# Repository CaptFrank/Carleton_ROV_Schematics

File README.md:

Carleton_ROV_Schematics
=======================

ROV schematics

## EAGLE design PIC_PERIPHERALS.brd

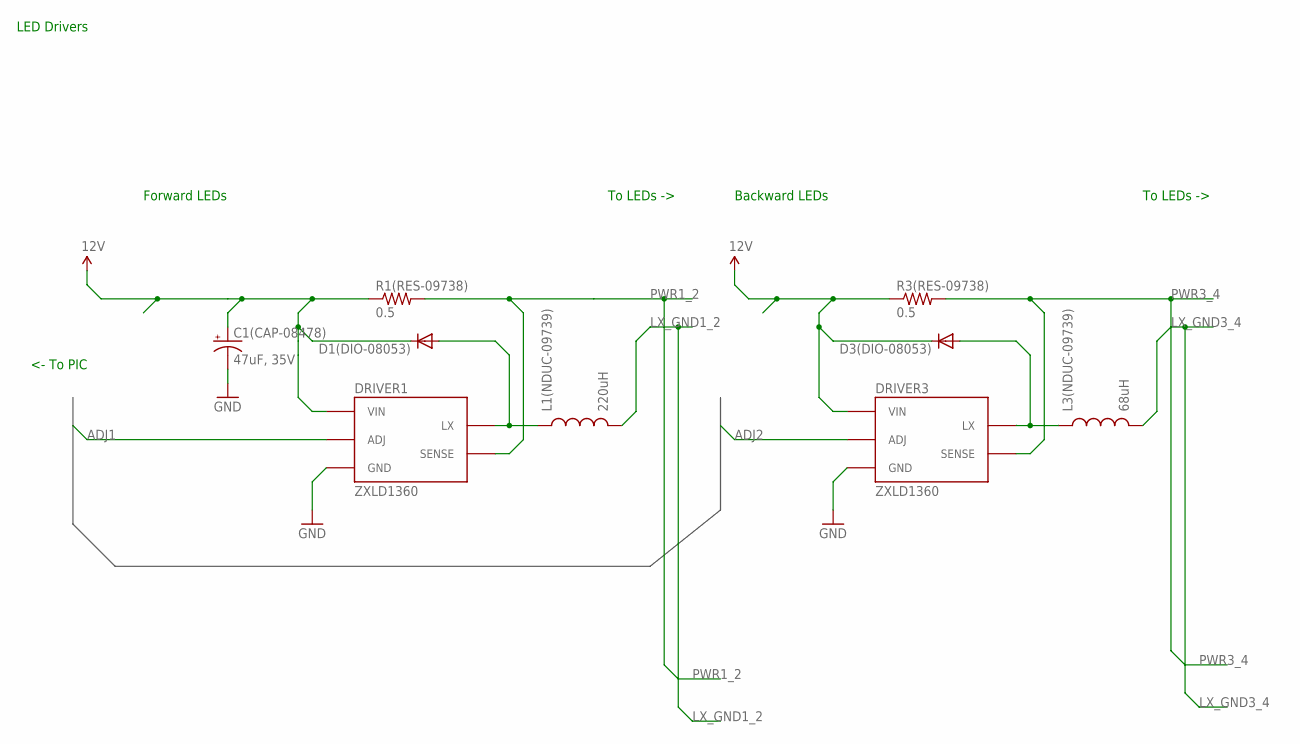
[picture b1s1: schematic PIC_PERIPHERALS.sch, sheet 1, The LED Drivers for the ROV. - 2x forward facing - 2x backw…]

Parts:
C1(CAP-08478): 47uF, 35V; EIA3216
D1(DIO-08053), D3(DIO-08053): DIODESMA; SMA-DIODE
DRIVER1, DRIVER3: ZXLD1360; SOT23-5
L1(NDUC-09739): 220uH; CDRH3D28
L3(NDUC-09739): 68uH; CDRH3D28
R1(RES-09738), R3(RES-09738): 0.5; 0805

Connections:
5V: D3(DIO-08053).C, DRIVER3.5 (VIN), R3(RES-09738).1; also elsewhere on the board
12V: C1(CAP-08478).A (+), D1(DIO-08053).C, DRIVER1.5 (VIN), R1(RES-09738).1
ADJ1: DRIVER1.3 (ADJ); also elsewhere on the board
ADJ2: DRIVER3.3 (ADJ); also elsewhere on the board
GND: C1(CAP-08478).C (-), DRIVER1.2 (GND), DRIVER3.2 (GND); also elsewhere on the board
LX_GND1_2: L1(NDUC-09739).2
LX_GND3_4: L3(NDUC-09739).2
unnamed: D1(DIO-08053).A, DRIVER1.1 (LX), L1(NDUC-09739).1
unnamed: D3(DIO-08053).A, DRIVER3.1 (LX), L3(NDUC-09739).1
PWR1_2: DRIVER1.4 (SENSE), R1(RES-09738).2
PWR3_4: DRIVER3.4 (SENSE), R3(RES-09738).2

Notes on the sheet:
LED Drivers
Forward LEDs
Backward LEDs
<- To PIC
To LEDs ->

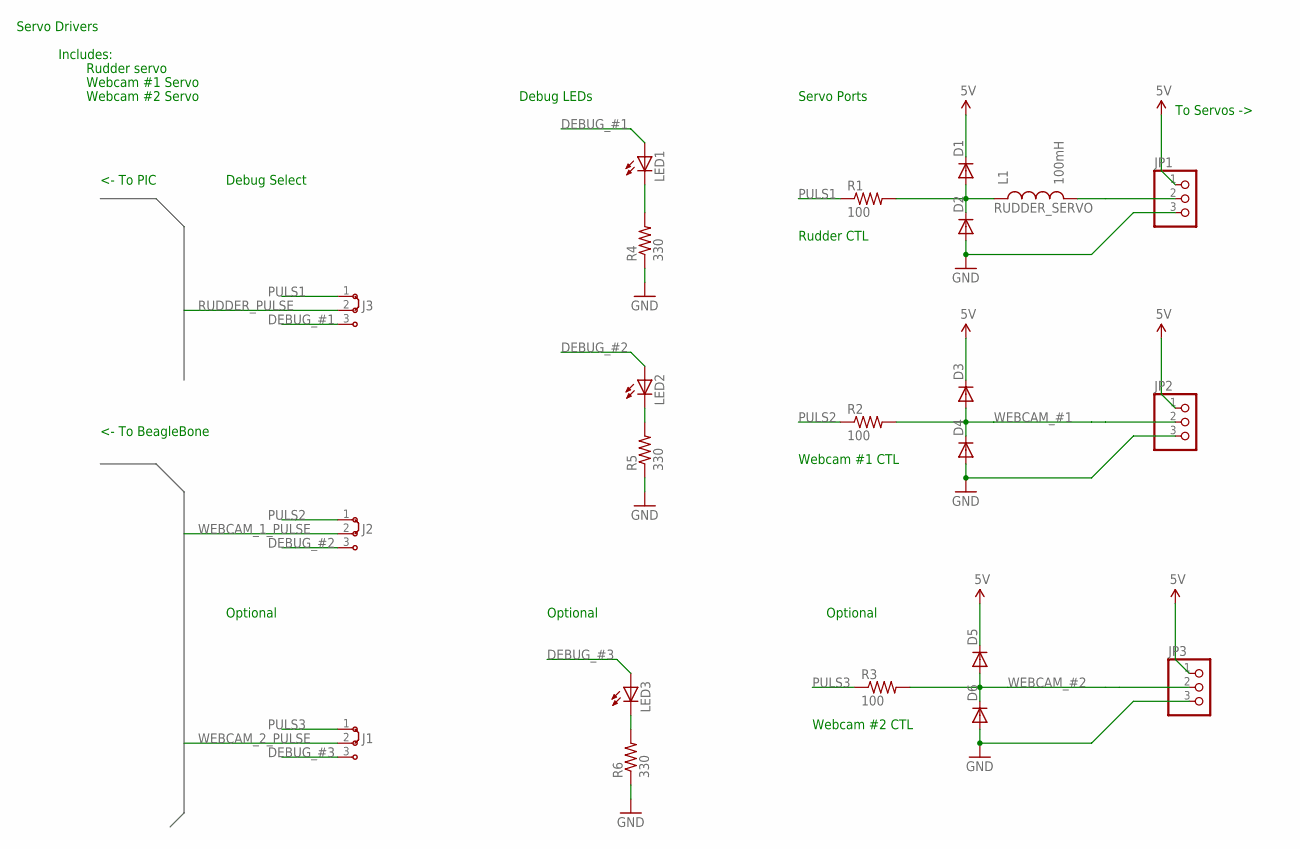
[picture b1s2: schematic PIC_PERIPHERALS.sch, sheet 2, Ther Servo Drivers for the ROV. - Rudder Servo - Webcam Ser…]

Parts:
D1, D2, D3, D4, D5, D6: DIODESMA-ALT; SMA-DIODE_ALT
J1, J2, J3: J2X2MM; 04C
JP1, JP2, JP3: PINHD-1X3CB; 1X03-CLEANBIG
L1: 100mH; 0805
LED1, LED2, LED3: LED; SMARTLED-TTW
R1, R2, R3: 100; 0402-RES
R4, R5, R6: 330; 0402-RES

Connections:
5V: D1.C, D3.C, D5.C, JP1.1, JP2.1, JP3.1; also elsewhere on the board
DEBUG_#1: J3.3, LED1.A@1 (A)
DEBUG_#2: J2.3, LED2.A@1 (A)
DEBUG_#3: J1.3, LED3.A@1 (A)
GND: D2.A, D4.A, D6.A, JP1.3, JP2.3, JP3.3, R4.1, R5.1, R6.1; also elsewhere on the board
unnamed: LED1.C@1 (C), R4.2
unnamed: LED2.C@1 (C), R5.2
unnamed: LED3.C@1 (C), R6.2
PULS1: J3.1, R1.1
PULS2: J2.1, R2.1
PULS3: J1.1, R3.1
RUDDER_PULSE: J3.2; also elsewhere on the board
RUDDER_SERVO: JP1.2, L1.2
RUDDER_SERVO1: D1.A, D2.C, L1.1, R1.2
WEBCAM_1_PULSE: J2.2; also elsewhere on the board
WEBCAM_2_PULSE: J1.2; also elsewhere on the board
WEBCAM_#1: D3.A, D4.C, JP2.2, R2.2
WEBCAM_#2: D5.A, D6.C, JP3.2, R3.2

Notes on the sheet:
Servo Drivers
Includes:
Rudder servo
Webcam #1 Servo
Webcam #2 Servo
To Servos ->
<- To PIC
Debug LEDs
Servo Ports
Debug Select
Rudder CTL
Webcam #1 CTL
Webcam #2 CTL
Optional
<- To BeagleBone

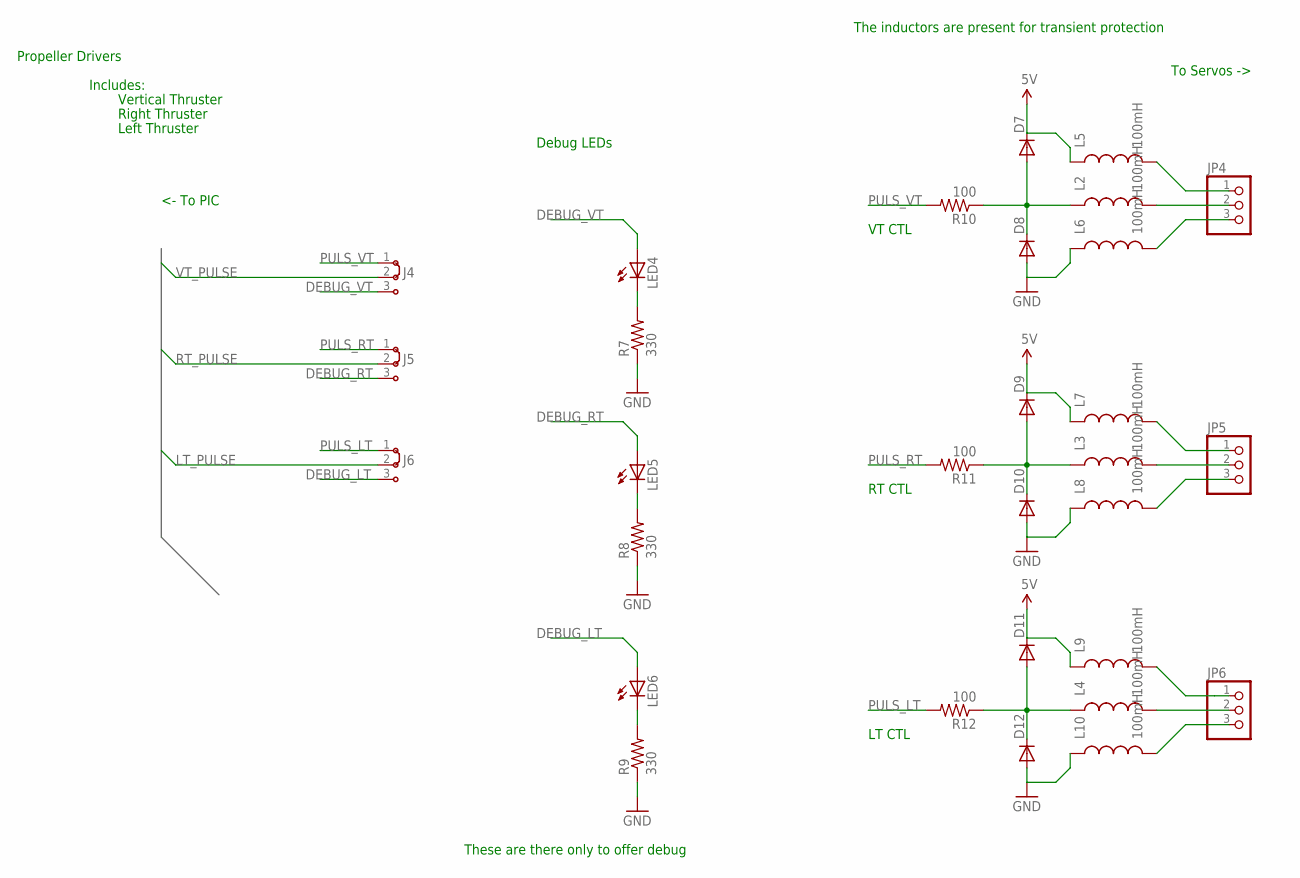
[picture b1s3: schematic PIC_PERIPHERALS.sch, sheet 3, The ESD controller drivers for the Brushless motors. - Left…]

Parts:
D7, D8, D9, D10, D11, D12: DIODESMA; SMA-DIODE
J4, J5, J6: J2X2MM; 04C
JP4, JP5, JP6: PINHD-1X3CB; 1X03-CLEANBIG
L2, L3, L4, L5, L6, L7, L8, L9, L10: 100mH; 0603
LED4, LED5, LED6: LED; SMARTLED-TTW
R7, R8, R9: 330; 0402-RES
R10, R11, R12: 100; 0402-RES

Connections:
5V: D7.C, D9.C, D11.C, L5.1, L7.1, L9.1; also elsewhere on the board
DEBUG_LT: J6.3, LED6.A@1 (A)
DEBUG_RT: J5.3, LED5.A@1 (A)
DEBUG_VT: J4.3, LED4.A@1 (A)
GND: D8.A, D10.A, D12.A, L6.1, L8.1, L10.1, R7.1, R8.1, R9.1; also elsewhere on the board
LT_PULSE: J6.2; also elsewhere on the board
unnamed: LED4.C@1 (C), R7.2
unnamed: LED5.C@1 (C), R8.2
unnamed: LED6.C@1 (C), R9.2
unnamed: D11.A, D12.C, L4.1, R12.1
unnamed: D9.A, D10.C, L3.1, R11.1
unnamed: D7.A, D8.C, L2.1, R10.1
unnamed: JP4.1, L5.2
unnamed: JP4.2, L2.2
unnamed: JP4.3, L6.2
unnamed: JP5.1, L7.2
unnamed: JP5.2, L3.2
unnamed: JP5.3, L8.2
unnamed: JP6.1, L9.2
unnamed: JP6.2, L4.2
unnamed: JP6.3, L10.2
PULS_LT: J6.1, R12.2
PULS_RT: J5.1, R11.2
PULS_VT: J4.1, R10.2
RT_PULSE: J5.2; also elsewhere on the board
VT_PULSE: J4.2; also elsewhere on the board

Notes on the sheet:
Propeller Drivers
Includes:
Vertical Thruster
Right Thruster
Left Thruster
To Servos ->
Debug LEDs
<- To PIC
VT CTL
LT CTL
RT CTL
The inductors are present for transient protection
These are there only to offer debug

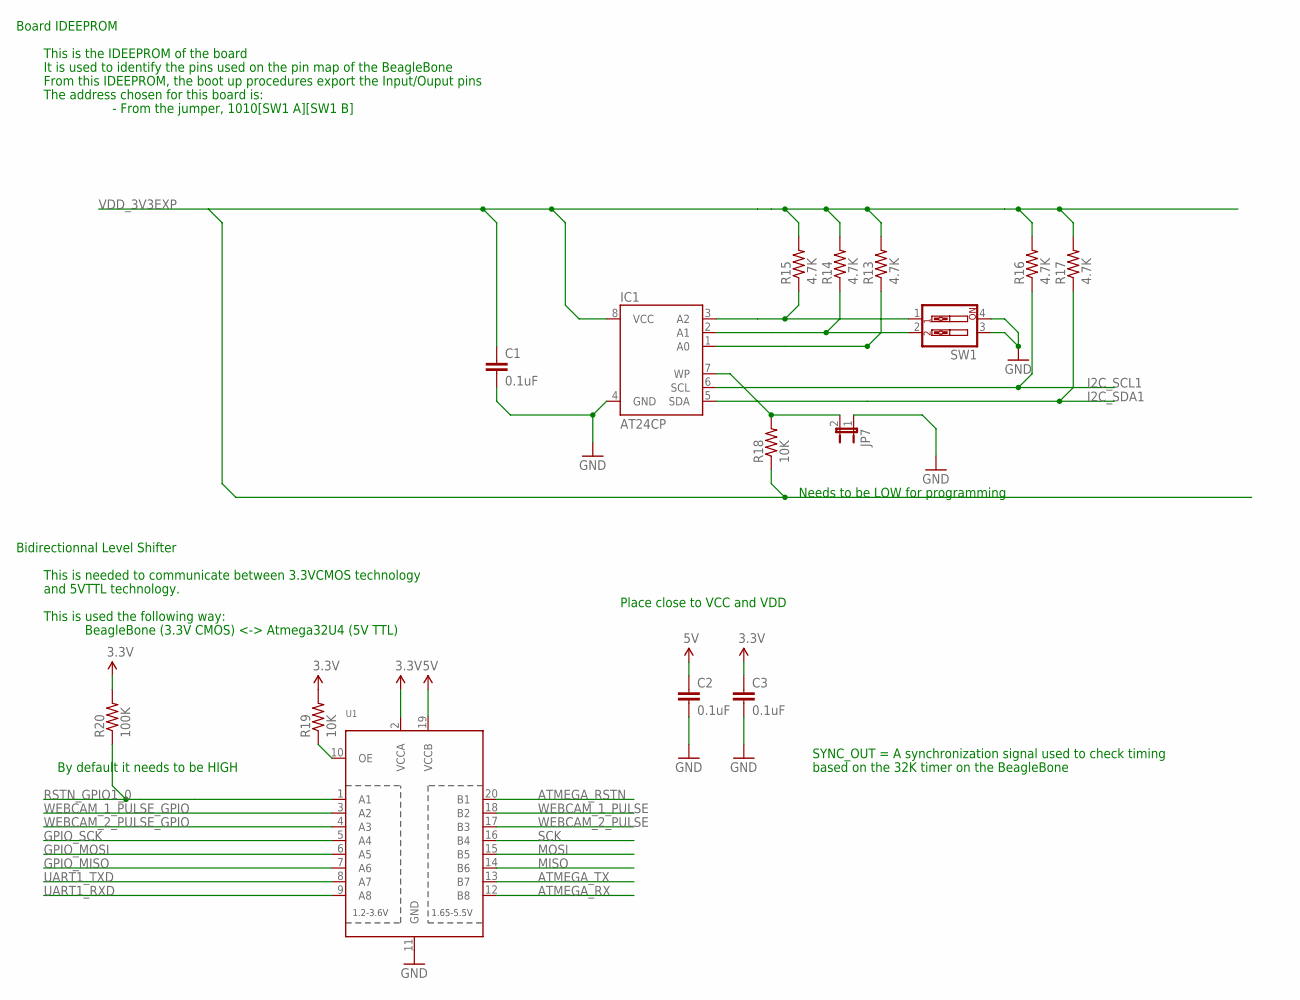
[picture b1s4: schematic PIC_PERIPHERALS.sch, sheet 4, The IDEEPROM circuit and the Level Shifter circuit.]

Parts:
C1, C2, C3: 0.1uF; 0402-CAP
IC1: AT24CP; DIL08
JP7: JUMPER-2PTH; 1X02
R13, R14, R15, R16, R17: 4.7K; 0402-RES
R18, R19: 10K; 0402-RES
R20: 100K; 0402-RES
SW1: SW_DIP-2; DIPSWITCH-02
U1: TXB0108PWR; TSSOP20

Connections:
3.3V: C3.1, R19.2, R20.2, U1.2 (VCCA); also elsewhere on the board
5V: C2.1, U1.19 (VCCB); also elsewhere on the board
ATMEGA_RSTN: U1.20 (B1); also elsewhere on the board
ATMEGA_RX: U1.12 (B8); also elsewhere on the board
ATMEGA_TX: U1.13 (B7); also elsewhere on the board
GND: C1.2, C2.2, C3.2, IC1.4 (GND), JP7.1, SW1.3, SW1.4, U1.11 (GND); also elsewhere on the board
GPIO_MISO: U1.7 (A6); also elsewhere on the board
GPIO_MOSI: U1.6 (A5); also elsewhere on the board
GPIO_SCK: U1.5 (A4); also elsewhere on the board
I2C_SCL1: IC1.6 (SCL), R16.1; also elsewhere on the board
I2C_SDA1: IC1.5 (SDA), R17.1; also elsewhere on the board
MISO: U1.14 (B6); also elsewhere on the board
MOSI: U1.15 (B5); also elsewhere on the board
unnamed: IC1.3 (A2), R15.1, SW1.1
unnamed: IC1.2 (A1), R14.1, SW1.2
unnamed: IC1.1 (A0), R13.1
unnamed: IC1.7 (WP), JP7.2, R18.2
unnamed: R19.1, U1.10 (OE)
RSTN_GPIO1_0: R20.1, U1.1 (A1); also elsewhere on the board
SCK: U1.16 (B4); also elsewhere on the board
UART1_RXD: U1.9 (A8); also elsewhere on the board
UART1_TXD: U1.8 (A7); also elsewhere on the board
VDD_3V3EXP: C1.1, IC1.8 (VCC), R13.2, R14.2, R15.2, R16.2, R17.2, R18.1
WEBCAM_1_PULSE: U1.18 (B2); also elsewhere on the board
WEBCAM_1_PULSE_GPIO: U1.3 (A2); also elsewhere on the board
WEBCAM_2_PULSE: U1.17 (B3); also elsewhere on the board
WEBCAM_2_PULSE_GPIO: U1.4 (A3); also elsewhere on the board

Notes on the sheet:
Board IDEEPROM
This is the IDEEPROM of the board
It is used to identify the pins used on the pin map of the BeagleBone
From this IDEEPROM, the boot up procedures export the Input/Ouput pins
The address chosen for this board is:
- From the jumper, 1010[SW1 A][SW1 B]
Needs to be LOW for programming
Bidirectionnal Level Shifter
This is needed to communicate between 3.3VCMOS technology
and 5VTTL technology.
This is used the following way:
BeagleBone (3.3V CMOS) <-> Atmega32U4 (5V TTL)
Place close to VCC and VDD
By default it needs to be HIGH
SYNC_OUT = A synchronization signal used to check timing
based on the 32K timer on the BeagleBone

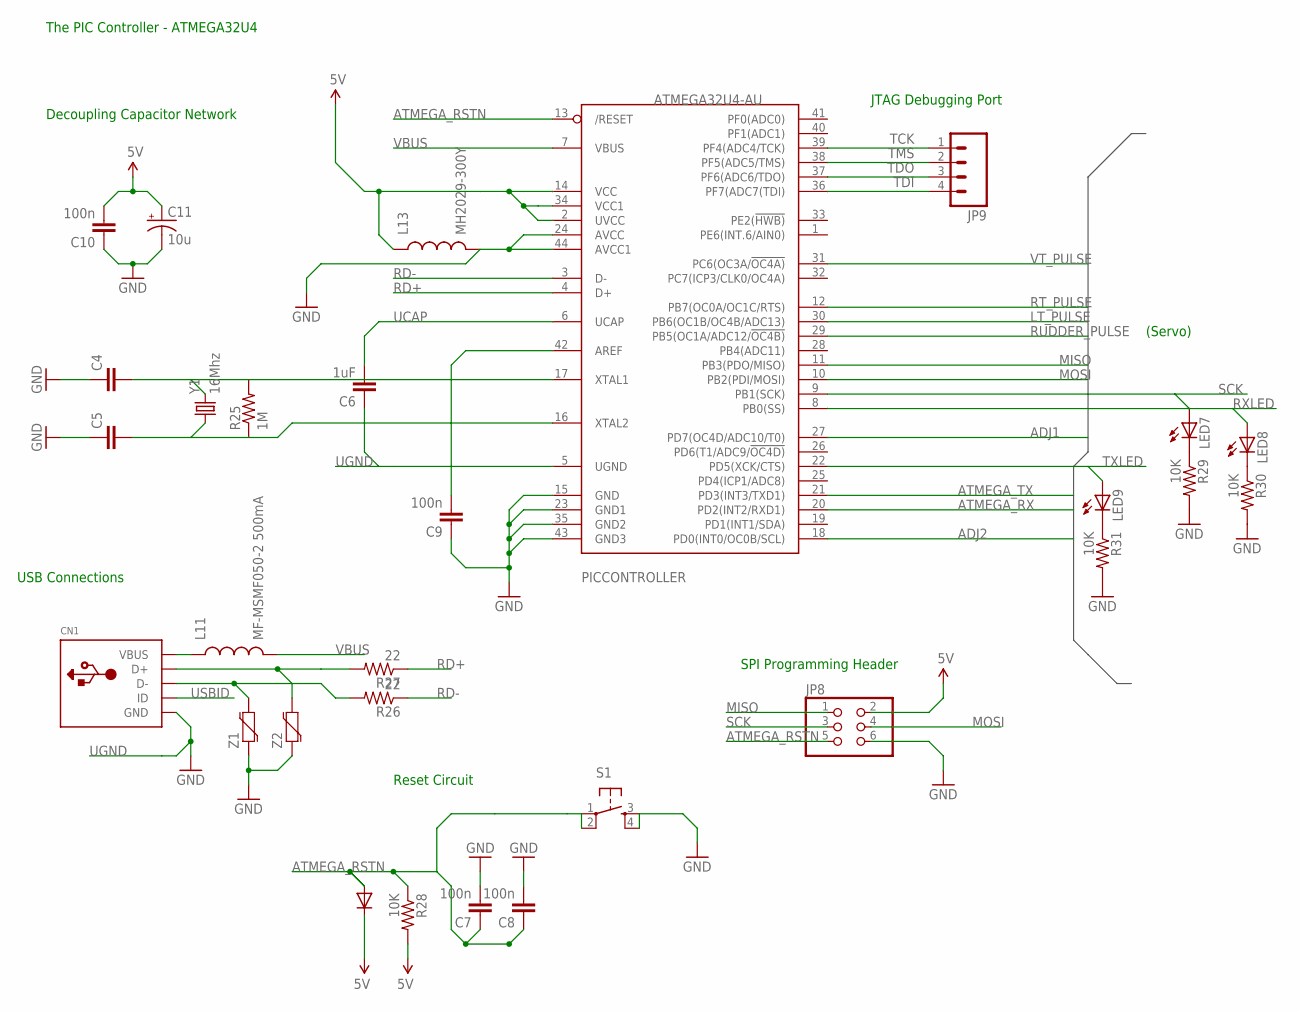
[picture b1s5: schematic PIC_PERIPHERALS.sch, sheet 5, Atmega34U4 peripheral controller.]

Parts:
C4, C5: CAP0402-CAP; 0402-CAP
C6: 1uF; 0402-CAP
C7, C8, C9, C10: 100n; 0402-CAP
C11: 10u; EIA3216
CN1: USBMINIB; USB-MINIB
JP8: PINHD-2X3; 2X03
JP9: M04SMD; 1X04-SMD
L11: MF-MSMF050-2 500mA; CDRH3D28
L13: MH2029-300Y; CDRH3D28
LED7, LED8, LED9: LED; SMARTLED-TTW
PICCONTROLLER: ATMEGA32U4-AU; TQFP44
R25: 1M; 0402-RES
R26, R27: 22; 0402-RES
R28, R29, R30, R31: 10K; 0402-RES
S1: TAC_SWITCHPTH; TACTILE-PTH
Y1: 16Mhz; CRYSTAL-SMD-5X3
Z1, Z2: VARISTOR-0402; 0402-RES

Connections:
5V: C10.2, C11.A (+), JP8.2, L13.1, PICCONTROLLER.2 (UVCC), PICCONTROLLER.14 (VCC), PICCONTROLLER.34 (VCC1), R28.2; also elsewhere on the board
ADJ1: PICCONTROLLER.27 (PD7(OC4D/ADC10/T0)); also elsewhere on the board
ADJ2: PICCONTROLLER.18 (PD0(INT0/OC0B/SCL)); also elsewhere on the board
ATMEGA_RSTN: C7.1, C8.1, JP8.5, PICCONTROLLER.13 (/RESET), R28.1, S1.1, S1.2; also elsewhere on the board
ATMEGA_RX: PICCONTROLLER.20 (PD2(INT2/RXD1)); also elsewhere on the board
ATMEGA_TX: PICCONTROLLER.21 (PD3(INT3/TXD1)); also elsewhere on the board
GND: C4.1, C5.1, C7.2, C8.2, C9.1, C10.1, C11.C (-), JP8.6, L13.2, PICCONTROLLER.15 (GND), PICCONTROLLER.23 (GND1), PICCONTROLLER.24 (AVCC), PICCONTROLLER.35 (GND2), PICCONTROLLER.43 (GND3), PICCONTROLLER.44 (AVCC1), R29.2, R30.2, R31.2, S1.3, S1.4, Z1.1, Z2.1; also elsewhere on the board
LT_PULSE: PICCONTROLLER.30 (PB6(OC1B/OC4B/ADC13)); also elsewhere on the board
MISO: JP8.1, PICCONTROLLER.11 (PB3(PDO/MISO)); also elsewhere on the board
MOSI: JP8.4, PICCONTROLLER.10 (PB2(PDI/MOSI)); also elsewhere on the board
unnamed: C4.2, PICCONTROLLER.17 (XTAL1), R25.2, Y1.3 (2)
unnamed: C5.2, PICCONTROLLER.16 (XTAL2), R25.1, Y1.1
unnamed: CN1.D-, R26.2, Z1.2
unnamed: CN1.D+, R27.2, Z2.2
unnamed: CN1.VBUS, L11.1
unnamed: C9.2, PICCONTROLLER.42 (AREF)
unnamed: LED7.C@1 (C), R29.1
unnamed: LED9.C@1 (C), R31.1
unnamed: LED8.C@1 (C), R30.1
RD+: PICCONTROLLER.4 (D+), R27.1
RD-: PICCONTROLLER.3 (D-), R26.1
RT_PULSE: PICCONTROLLER.12 (PB7(OC0A/OC1C/RTS)); also elsewhere on the board
RUDDER_PULSE: PICCONTROLLER.29 (PB5(OC1A/ADC12/!OC4B)); also elsewhere on the board
RXLED: PICCONTROLLER.8 (PB0(SS))
SCK: JP8.3, LED7.A@1 (A), PICCONTROLLER.9 (PB1(SCK)); also elsewhere on the board
TCK: JP9.1, PICCONTROLLER.39 (PF4(ADC4/TCK))
TDI: JP9.4, PICCONTROLLER.36 (PF7(ADC7(TDI))
TDO: JP9.3, PICCONTROLLER.37 (PF6(ADC6/TDO))
TMS: JP9.2, PICCONTROLLER.38 (PF5(ADC5/TMS))
TXLED: PICCONTROLLER.22 (PD5(XCK/CTS))
UCAP: C6.2, PICCONTROLLER.6 (UCAP)
UGND: C6.1, CN1.GND, PICCONTROLLER.5 (UGND)
USBID: CN1.ID
VBUS: L11.2, PICCONTROLLER.7 (VBUS)
VT_PULSE: PICCONTROLLER.31 (PC6(OC3A/!OC4A)); also elsewhere on the board

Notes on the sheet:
The PIC Controller - ATMEGA32U4
USB Connections
Reset Circuit
SPI Programming Header
(Servo)
JTAG Debugging Port
Decoupling Capacitor Network

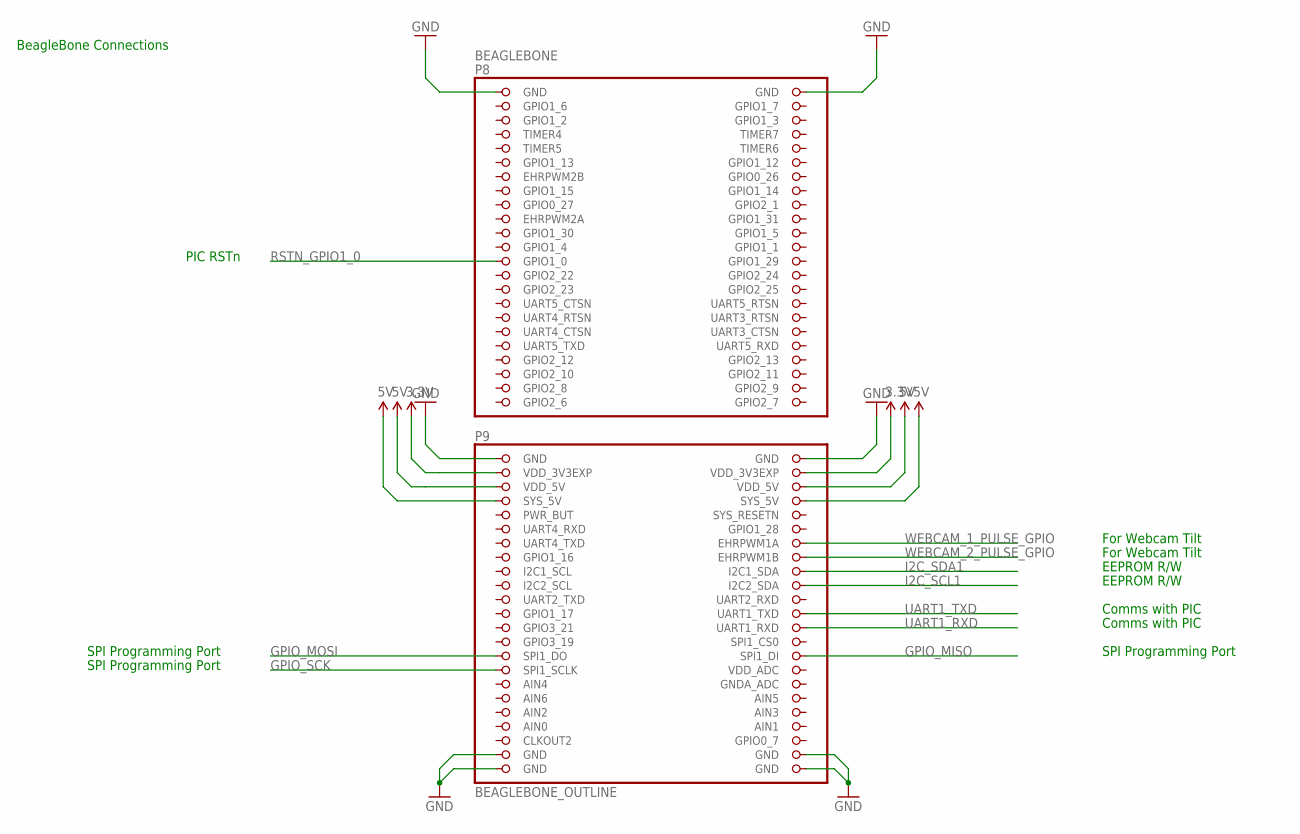
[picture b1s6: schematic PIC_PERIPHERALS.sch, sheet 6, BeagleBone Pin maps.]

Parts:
BEAGLEBONE: BEAGLEBONE_OUTLINE; BEAGLEBONE_SHIELD

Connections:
3.3V: BEAGLEBONE.49 (VDD_3V3EXP), BEAGLEBONE.50 (VDD_3V3EXP); also elsewhere on the board
5V: BEAGLEBONE.51 (VDD_5V), BEAGLEBONE.52 (VDD_5V), BEAGLEBONE.53 (SYS_5V), BEAGLEBONE.54 (SYS_5V); also elsewhere on the board
AIN0: BEAGLEBONE.85 (AIN0)
GND: BEAGLEBONE.1 (GND), BEAGLEBONE.2 (GND), BEAGLEBONE.47 (GND), BEAGLEBONE.48 (GND), BEAGLEBONE.89 (GND), BEAGLEBONE.90 (GND), BEAGLEBONE.91 (GND), BEAGLEBONE.92 (GND); also elsewhere on the board
GPIO_MISO: BEAGLEBONE.76 (SPI1_DI); also elsewhere on the board
GPIO_MOSI: BEAGLEBONE.75 (SPI1_DO); also elsewhere on the board
GPIO_SCK: BEAGLEBONE.77 (SPI1_SCLK); also elsewhere on the board
I2C_SCL1: BEAGLEBONE.66 (I2C2_SDA); also elsewhere on the board
I2C_SDA1: BEAGLEBONE.64 (I2C1_SDA); also elsewhere on the board
RSTN_GPIO1_0: BEAGLEBONE.25 (GPIO1_0); also elsewhere on the board
UART1_RXD: BEAGLEBONE.72 (UART1_RXD); also elsewhere on the board
UART1_TXD: BEAGLEBONE.70 (UART1_TXD); also elsewhere on the board
WEBCAM_1_PULSE_GPIO: BEAGLEBONE.60 (EHRPWM1A); also elsewhere on the board
WEBCAM_2_PULSE_GPIO: BEAGLEBONE.62 (EHRPWM1B); also elsewhere on the board

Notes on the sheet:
BeagleBone Connections
For Webcam Tilt
EEPROM R/W
Comms with PIC
PIC RSTn
SPI Programming Port

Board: 2 copper layers, 105 parts (0 on the bottom side), 90 nets, no tracks yet.

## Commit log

2013-05-22 Initial Commit of the schematics
    initial commit of file structure
2013-05-23 added some initial frameworks
2013-05-23 started the I2C cape

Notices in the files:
parts and their libraries:
SparkFun: Licensing: CC v3.0 Share-Alike You are welcome to use this library for commercial purposes.
